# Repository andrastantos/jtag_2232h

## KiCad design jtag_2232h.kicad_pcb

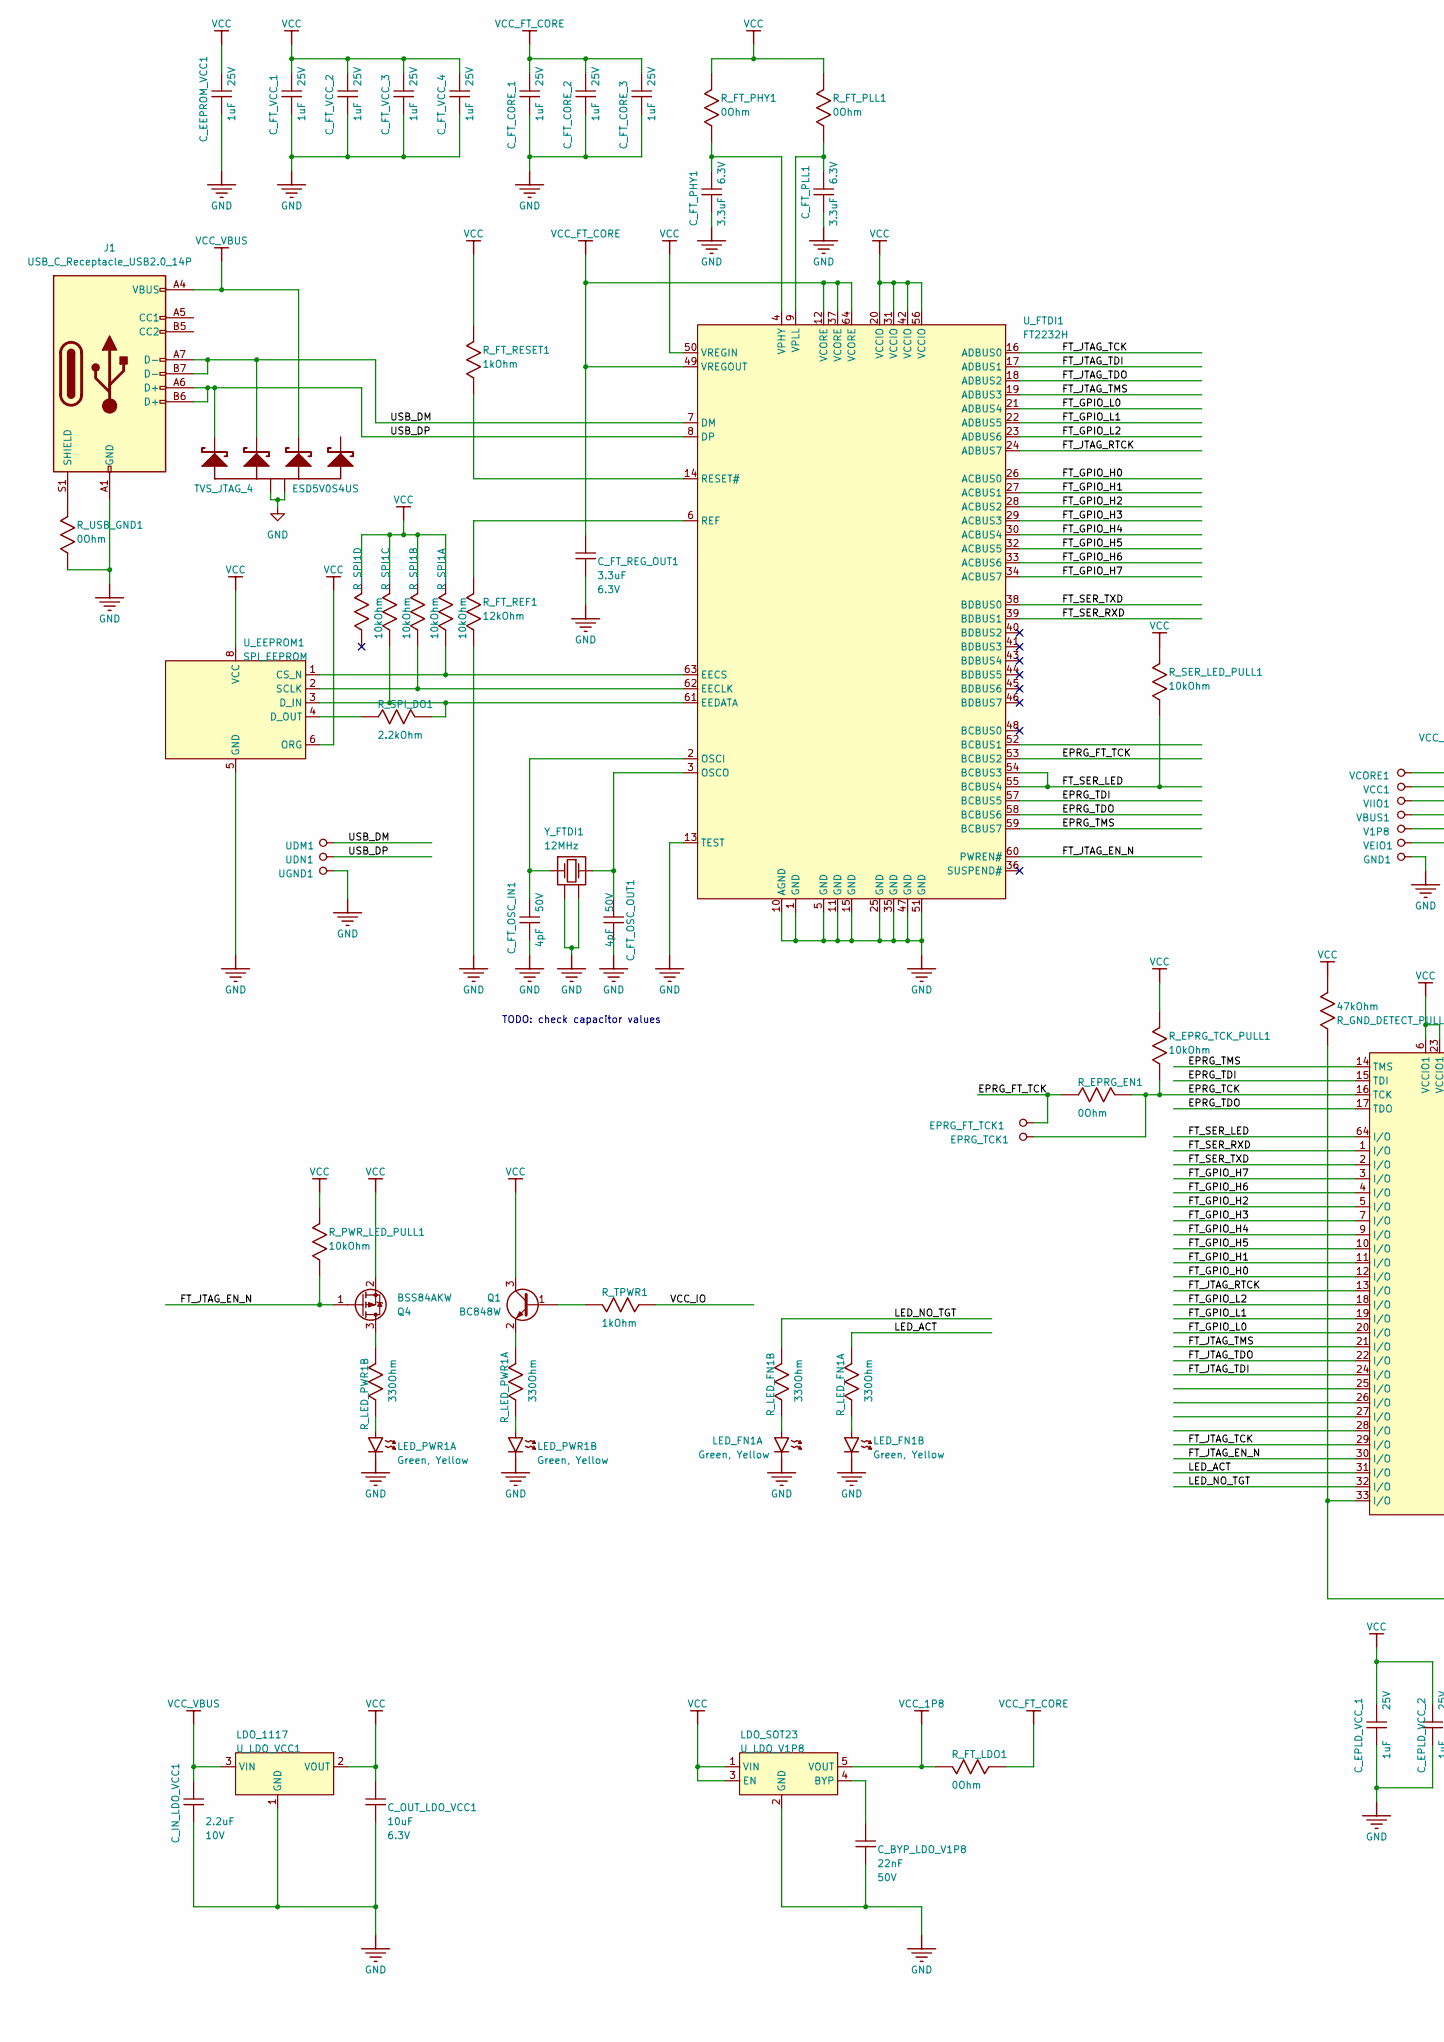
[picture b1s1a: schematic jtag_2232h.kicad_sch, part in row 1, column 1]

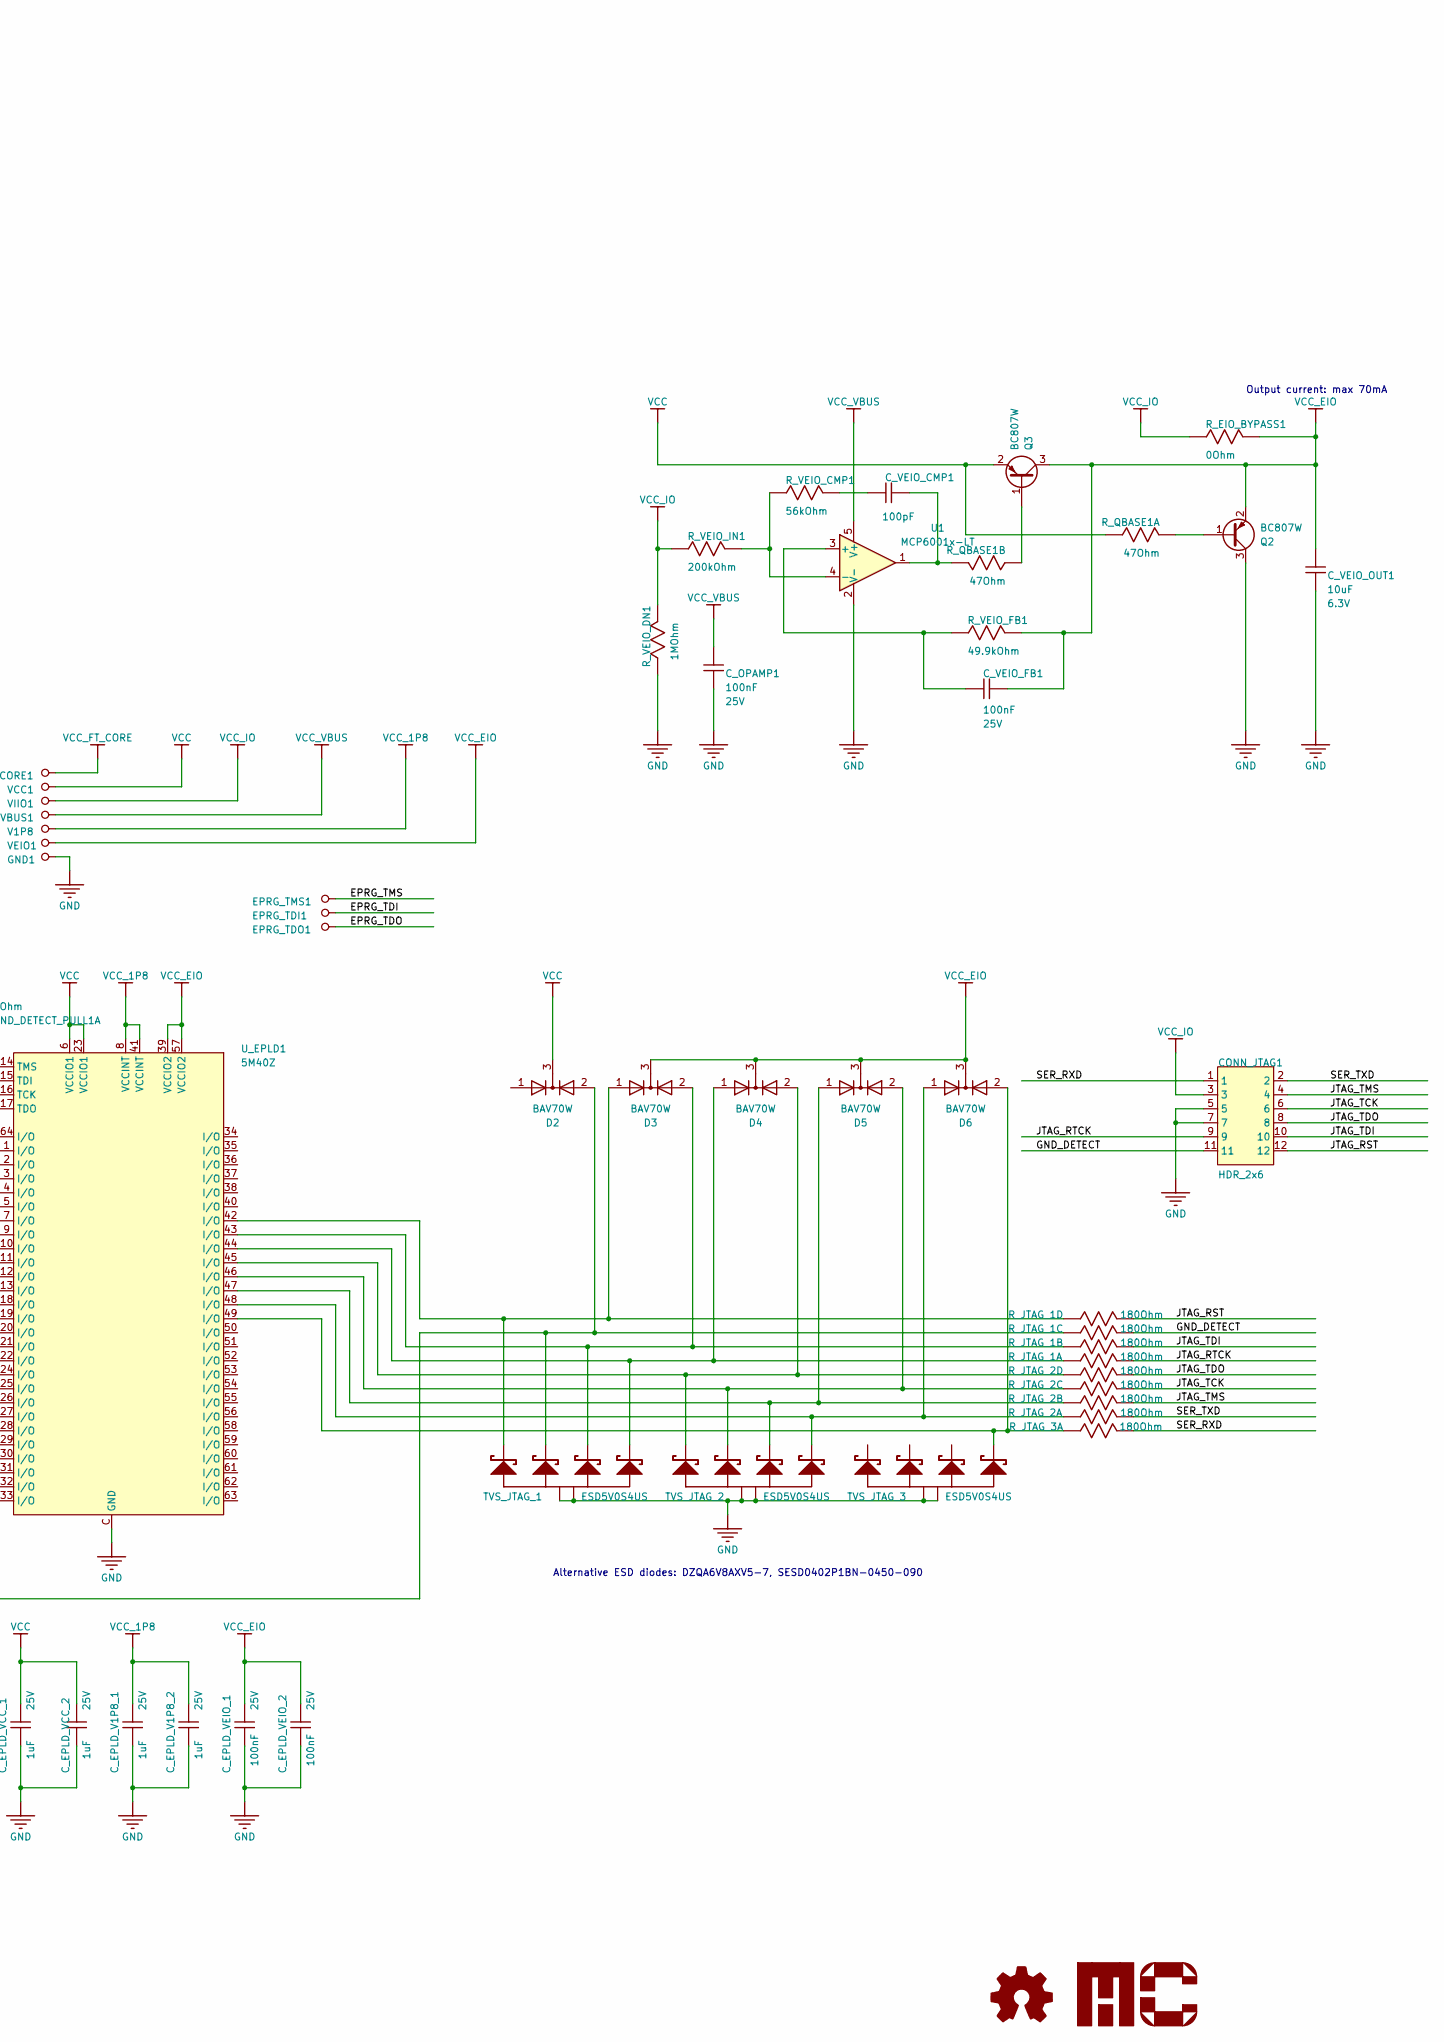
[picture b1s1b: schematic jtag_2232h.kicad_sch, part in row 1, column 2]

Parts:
CONN_JTAG1: HDR_2x6; RCP_1P27_2X6_EDGE; MANUFACTURER PART NUMBER M50-3000645
C_BYP_LDO_V1P8: 22nF; C_0603_1608Metric_Pad1.08x0.95mm_HandSolder; VOLTAGE - RATED 50V; TOLERANCE +/-20%; MANUFACTURER PART NUMBER C1608X7R1H223M; DIGI-KEY PART NUMBER 445-5092-1-ND
C_EEPROM_VCC1: 1uF; C_0603_1608Metric_Pad1.08x0.95mm_HandSolder; VOLTAGE - RATED 25V; TOLERANCE +/-10%; MANUFACTURER PART NUMBER C1608X5R1E105K; DIGI-KEY PART NUMBER 445-5146-1-ND
C_EPLD_V1P8_1, C_EPLD_V1P8_2: 1uF; C_0603_1608Metric_Pad1.08x0.95mm_HandSolder; VOLTAGE - RATED 25V; TOLERANCE +/-10%; MANUFACTURER PART NUMBER C1608X5R1E105K; DIGI-KEY PART NUMBER 445-5146-1-ND
C_EPLD_VCC_1, C_EPLD_VCC_2: 1uF; C_0603_1608Metric_Pad1.08x0.95mm_HandSolder; VOLTAGE - RATED 25V; TOLERANCE +/-10%; MANUFACTURER PART NUMBER C1608X5R1E105K; DIGI-KEY PART NUMBER 445-5146-1-ND
C_EPLD_VEIO_1, C_EPLD_VEIO_2: 100nF; C_0603_1608Metric_Pad1.08x0.95mm_HandSolder; VOLTAGE - RATED 25V; TOLERANCE +/-10%; MANUFACTURER PART NUMBER C1608X7R1E104K; DIGI-KEY PART NUMBER 445-1316-1-ND
C_FT_CORE_1, C_FT_CORE_2, C_FT_CORE_3: 1uF; C_0603_1608Metric_Pad1.08x0.95mm_HandSolder; VOLTAGE - RATED 25V; TOLERANCE +/-10%; MANUFACTURER PART NUMBER C1608X5R1E105K; DIGI-KEY PART NUMBER 445-5146-1-ND
C_FT_OSC_IN1: 4pF; C_0603_1608Metric_Pad1.08x0.95mm_HandSolder; VOLTAGE - RATED 50V; TOLERANCE +/-0.25pF; MANUFACTURER PART NUMBER C1608C0G1H040C; DIGI-KEY PART NUMBER 445-5029-1-ND
C_FT_OSC_OUT1: 4pF; C_0603_1608Metric_Pad1.08x0.95mm_HandSolder; VOLTAGE - RATED 50V; TOLERANCE +/-0.25pF; MANUFACTURER PART NUMBER C1608C0G1H040C; DIGI-KEY PART NUMBER 445-5029-1-ND
C_FT_PHY1: 3.3uF; C_0603_1608Metric_Pad1.08x0.95mm_HandSolder; VOLTAGE - RATED 6.3V; TOLERANCE +/-10%; MANUFACTURER PART NUMBER C1608X5R0J335K; DIGI-KEY PART NUMBER 445-5176-1-ND
C_FT_PLL1: 3.3uF; C_0603_1608Metric_Pad1.08x0.95mm_HandSolder; VOLTAGE - RATED 6.3V; TOLERANCE +/-10%; MANUFACTURER PART NUMBER C1608X5R0J335K; DIGI-KEY PART NUMBER 445-5176-1-ND
C_FT_REG_OUT1: 3.3uF; C_0603_1608Metric_Pad1.08x0.95mm_HandSolder; VOLTAGE - RATED 6.3V; TOLERANCE +/-10%; MANUFACTURER PART NUMBER C1608X5R0J335K; DIGI-KEY PART NUMBER 445-5176-1-ND
C_FT_VCC_1, C_FT_VCC_2, C_FT_VCC_3, C_FT_VCC_4: 1uF; C_0603_1608Metric_Pad1.08x0.95mm_HandSolder; VOLTAGE - RATED 25V; TOLERANCE +/-10%; MANUFACTURER PART NUMBER C1608X5R1E105K; DIGI-KEY PART NUMBER 445-5146-1-ND
C_IN_LDO_VCC1: 2.2uF; C_0603_1608Metric_Pad1.08x0.95mm_HandSolder; VOLTAGE - RATED 10V; TOLERANCE +/-10%; MANUFACTURER PART NUMBER C1608X5R1A225K; DIGI-KEY PART NUMBER 445-5166-1-ND
C_OPAMP1: 100nF; C_0603_1608Metric_Pad1.08x0.95mm_HandSolder; VOLTAGE - RATED 25V; TOLERANCE +/-10%; MANUFACTURER PART NUMBER C1608X7R1E104K; DIGI-KEY PART NUMBER 445-1316-1-ND
C_OUT_LDO_VCC1: 10uF; C_0603_1608Metric_Pad1.08x0.95mm_HandSolder; VOLTAGE - RATED 6.3V; TOLERANCE +/-20%; MANUFACTURER PART NUMBER C1608X5R0J106M; DIGI-KEY PART NUMBER 445-4112-1-ND
C_VEIO_CMP1: 100pF; C_0603_1608Metric_Pad1.08x0.95mm_HandSolder; VOLTAGE - RATED 50V; TOLERANCE +/-5%; MANUFACTURER PART NUMBER C1608C0G1H101J; DIGI-KEY PART NUMBER 445-1281-1-ND
C_VEIO_FB1: 100nF; C_0603_1608Metric_Pad1.08x0.95mm_HandSolder; VOLTAGE - RATED 25V; TOLERANCE +/-10%; MANUFACTURER PART NUMBER C1608X7R1E104K; DIGI-KEY PART NUMBER 445-1316-1-ND
C_VEIO_OUT1: 10uF; C_0603_1608Metric_Pad1.08x0.95mm_HandSolder; VOLTAGE - RATED 6.3V; TOLERANCE +/-20%; MANUFACTURER PART NUMBER C1608X5R0J106M; DIGI-KEY PART NUMBER 445-4112-1-ND
D2, D3, D4, D5, D6: BAV70W; SOT-323_SC-70
EPRG_FT_TCK1: Test_Point; TEST_POINT_100
EPRG_TCK1: Test_Point; TEST_POINT_100
EPRG_TDI1: Test_Point; TEST_POINT_100
EPRG_TDO1: Test_Point; TEST_POINT_100
EPRG_TMS1: Test_Point; TEST_POINT_100
GND1: Test_Point; TEST_POINT_100
J1: USB_C_Receptacle_USB2.0_14P; USB_C_Receptacle_HRO_TYPE-C-31-M-12; mpn USB4215-03-A
LED_FN1: LED_2; LEDX2_150X160X55; MANUFACTURER PART NUMBER APTB1612YSGC-F01
LED_PWR1: LED_2; LEDX2_150X160X55; MANUFACTURER PART NUMBER APTB1612YSGC-F01
LOGO1: MC_logo_micro
Q1: BC848W; SOT-323_SC-70
Q2, Q3: BC807W; SOT-323_SC-70
Q4: BSS84AKW; SOT-323_SC-70
R_EIO_BYPASS1: 0Ohm; R_0603_1608Metric_Pad0.98x0.95mm_HandSolder; TOLERANCE Jumper; MANUFACTURER PART NUMBER RMCF0603ZT0R00; DIGI-KEY PART NUMBER RMCF0603ZT0R00CT-ND
R_EPRG_EN1: 0Ohm; R_0603_1608Metric_Pad0.98x0.95mm_HandSolder; TOLERANCE Jumper; MANUFACTURER PART NUMBER RMCF0603ZT0R00; DIGI-KEY PART NUMBER RMCF0603ZT0R00CT-ND
R_EPRG_TCK_PULL1: 10kOhm; R_0603_1608Metric_Pad0.98x0.95mm_HandSolder; TOLERANCE +/-1%; MANUFACTURER PART NUMBER RMCF0603FT10K0; DIGI-KEY PART NUMBER RMCF0603FT10K0CT-ND
R_FT_LDO1: 0Ohm; R_0603_1608Metric_Pad0.98x0.95mm_HandSolder; TOLERANCE Jumper; MANUFACTURER PART NUMBER RMCF0603ZT0R00; DIGI-KEY PART NUMBER RMCF0603ZT0R00CT-ND
R_FT_PHY1: 0Ohm; R_0603_1608Metric_Pad0.98x0.95mm_HandSolder; TOLERANCE Jumper; MANUFACTURER PART NUMBER RMCF0603ZT0R00; DIGI-KEY PART NUMBER RMCF0603ZT0R00CT-ND
R_FT_PLL1: 0Ohm; R_0603_1608Metric_Pad0.98x0.95mm_HandSolder; TOLERANCE Jumper; MANUFACTURER PART NUMBER RMCF0603ZT0R00; DIGI-KEY PART NUMBER RMCF0603ZT0R00CT-ND
R_FT_REF1: 12kOhm; R_0603_1608Metric_Pad0.98x0.95mm_HandSolder; TOLERANCE +/-1%; MANUFACTURER PART NUMBER RMCF0603FT12K0; DIGI-KEY PART NUMBER RMCF0603FT12K0CT-ND
R_FT_RESET1: 1kOhm; R_0603_1608Metric_Pad0.98x0.95mm_HandSolder; TOLERANCE +/-1%; MANUFACTURER PART NUMBER RMCF0603FT1K00; DIGI-KEY PART NUMBER RMCF0603FT1K00CT-ND
R_GND_DETECT_PULL1: 47kOhm; R_Array_Convex_2x0603; TOLERANCE +/-5%; MANUFACTURER PART NUMBER EXB-V4V473JV; DIGI-KEY PART NUMBER Y2473CT-ND
R_JTAG_1, R_JTAG_2: 180Ohm; R_Array_Convex_4x0603; TOLERANCE +/-5%; MANUFACTURER PART NUMBER EXB-V8V181JV; DIGI-KEY PART NUMBER Y4181CT-ND
R_JTAG_3: 180Ohm; R_Array_Convex_2x0603; TOLERANCE +/-5%; MANUFACTURER PART NUMBER EXB-V4V181JV; DIGI-KEY PART NUMBER Y2181CT-ND
R_LED_FN1: 330Ohm; R_Array_Convex_2x0603; TOLERANCE +/-5%; MANUFACTURER PART NUMBER EXB-V4V331JV; DIGI-KEY PART NUMBER Y2331CT-ND
R_LED_PWR1: 330Ohm; R_Array_Convex_2x0603; TOLERANCE +/-5%; MANUFACTURER PART NUMBER EXB-V4V331JV; DIGI-KEY PART NUMBER Y2331CT-ND
R_PWR_LED_PULL1: 10kOhm; R_0603_1608Metric_Pad0.98x0.95mm_HandSolder; TOLERANCE +/-1%; MANUFACTURER PART NUMBER RMCF0603FT10K0; DIGI-KEY PART NUMBER RMCF0603FT10K0CT-ND
R_QBASE1: 47Ohm; R_Array_Convex_2x0603; TOLERANCE +/-5%; MANUFACTURER PART NUMBER EXB-V4V470JV; DIGI-KEY PART NUMBER Y2470CT-ND
R_SER_LED_PULL1: 10kOhm; R_0603_1608Metric_Pad0.98x0.95mm_HandSolder; TOLERANCE +/-1%; MANUFACTURER PART NUMBER RMCF0603FT10K0; DIGI-KEY PART NUMBER RMCF0603FT10K0CT-ND
R_SPI1: 10kOhm; R_Array_Convex_4x0603; TOLERANCE +/-5%; MANUFACTURER PART NUMBER EXB-V8V103JV; DIGI-KEY PART NUMBER Y4103CT-ND
R_SPI_DO1: 2.2kOhm; R_0603_1608Metric_Pad0.98x0.95mm_HandSolder; TOLERANCE +/-5%; MANUFACTURER PART NUMBER RMCF0603JT2K20; DIGI-KEY PART NUMBER RMCF0603JT2K20CT-ND
R_TPWR1: 1kOhm; R_0603_1608Metric_Pad0.98x0.95mm_HandSolder; TOLERANCE +/-1%; MANUFACTURER PART NUMBER RMCF0603FT1K00; DIGI-KEY PART NUMBER RMCF0603FT1K00CT-ND
R_USB_GND1: 0Ohm; R_0603_1608Metric_Pad0.98x0.95mm_HandSolder; TOLERANCE Jumper; MANUFACTURER PART NUMBER RMCF0603ZT0R00; DIGI-KEY PART NUMBER RMCF0603ZT0R00CT-ND
R_VEIO_CMP1: 56kOhm; R_0603_1608Metric_Pad0.98x0.95mm_HandSolder; TOLERANCE +/-5%; MANUFACTURER PART NUMBER RMCF0603JG56K0; DIGI-KEY PART NUMBER RMCF0603JG56K0CT-ND
R_VEIO_DN1: 1MOhm; R_0603_1608Metric_Pad0.98x0.95mm_HandSolder; TOLERANCE +/-1%; MANUFACTURER PART NUMBER RMCF0603FT1M00; DIGI-KEY PART NUMBER RMCF0603FT1M00CT-ND
R_VEIO_FB1: 49.9kOhm; R_0603_1608Metric_Pad0.98x0.95mm_HandSolder; TOLERANCE +/-1%; MANUFACTURER PART NUMBER RMCF0603FT49K9; DIGI-KEY PART NUMBER RMCF0603FT49K9CT-ND
R_VEIO_IN1: 200kOhm; R_0603_1608Metric_Pad0.98x0.95mm_HandSolder; TOLERANCE +/-5%; MANUFACTURER PART NUMBER RMCF0603JT200K; DIGI-KEY PART NUMBER RMCF0603JT200KCT-ND
TVS_JTAG_1, TVS_JTAG_2, TVS_JTAG_3, TVS_JTAG_4: ESD5V0S4US; SOT-363_SC-70-6
U1: MCP6001x-LT; SOT-353_SC-70-5
UDM1: Test_Point; TEST_POINT_100
UDN1: Test_Point; TEST_POINT_100
UGND1: Test_Point; TEST_POINT_100
U_EEPROM1: SPI_EEPROM; TSSOP-8_4.4x3mm_P0.65mm; MANUFACTURER PART NUMBER AT93C46D-TH-B
U_EPLD1: 5M40Z; TSQFP40P900X900X120_HS_64N
U_FTDI1: FT2232H; LQFP-64_10x10mm_P0.5mm
U_LDO_V1P8: LDO_SOT23; SOT-23-5; OUTPUT VOLTAGE (V) 1.8; INPUT VOLTAGE MIN (V) 1.8; MANUFACTURER PART NUMBER PT7M8206B18TA5EX
U_LDO_VCC1: LDO_1117; SOT-89-3_Handsoldering; OUTPUT VOLTAGE (V) 3.3; INPUT VOLTAGE MIN (V) 2.75; MANUFACTURER PART NUMBER AP1117Y33G-13
V1P8: Test_Point; TEST_POINT_100
VBUS1: Test_Point; TEST_POINT_100
VCC1: Test_Point; TEST_POINT_100
VCORE1: Test_Point; TEST_POINT_100
VEIO1: Test_Point; TEST_POINT_100
VIIO1: Test_Point; TEST_POINT_100
Y_FTDI1: XTAL_4P; XTAL_4P_3P2x2P5; TOLERANCE 15ppm

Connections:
/EPRG_FT_TCK: EPRG_FT_TCK1.1, R_EPRG_EN1.1, U_FTDI1.53 (BCBUS2)
/EPRG_TCK: EPRG_TCK1.1, R_EPRG_EN1.2, R_EPRG_TCK_PULL1.1, U_EPLD1.16 (TCK)
/EPRG_TDI: EPRG_TDI1.1, U_EPLD1.15 (TDI), U_FTDI1.57 (BCBUS5)
/EPRG_TDO: EPRG_TDO1.1, U_EPLD1.17 (TDO), U_FTDI1.58 (BCBUS6)
/EPRG_TMS: EPRG_TMS1.1, U_EPLD1.14 (TMS), U_FTDI1.59 (BCBUS7)
/FT_GPIO_H0: U_EPLD1.12 (I/O), U_FTDI1.26 (ACBUS0)
/FT_GPIO_H1: U_EPLD1.11 (I/O), U_FTDI1.27 (ACBUS1)
/FT_GPIO_H2: U_EPLD1.5 (I/O), U_FTDI1.28 (ACBUS2)
/FT_GPIO_H3: U_EPLD1.7 (I/O), U_FTDI1.29 (ACBUS3)
/FT_GPIO_H4: U_EPLD1.9 (I/O), U_FTDI1.30 (ACBUS4)
/FT_GPIO_H5: U_EPLD1.10 (I/O), U_FTDI1.32 (ACBUS5)
/FT_GPIO_H6: U_EPLD1.4 (I/O), U_FTDI1.33 (ACBUS6)
/FT_GPIO_H7: U_EPLD1.3 (I/O), U_FTDI1.34 (ACBUS7)
/FT_GPIO_L0: U_EPLD1.20 (I/O), U_FTDI1.21 (ADBUS4)
/FT_GPIO_L1: U_EPLD1.19 (I/O), U_FTDI1.22 (ADBUS5)
/FT_GPIO_L2: U_EPLD1.18 (I/O), U_FTDI1.23 (ADBUS6)
/FT_JTAG_EN_N: Q4.1 (G), R_PWR_LED_PULL1.1, U_EPLD1.30 (I/O), U_FTDI1.60 (PWREN#)
/FT_JTAG_RTCK: U_EPLD1.13 (I/O), U_FTDI1.24 (ADBUS7)
/FT_JTAG_TCK: U_EPLD1.29 (I/O), U_FTDI1.16 (ADBUS0)
/FT_JTAG_TDI: U_EPLD1.24 (I/O), U_FTDI1.17 (ADBUS1)
/FT_JTAG_TDO: U_EPLD1.22 (I/O), U_FTDI1.18 (ADBUS2)
/FT_JTAG_TMS: U_EPLD1.21 (I/O), U_FTDI1.19 (ADBUS3)
/FT_SER_LED: R_SER_LED_PULL1.1, U_EPLD1.64 (I/O), U_FTDI1.54 (BCBUS3), U_FTDI1.55 (BCBUS4)
/FT_SER_RXD: U_EPLD1.1 (I/O), U_FTDI1.39 (BDBUS1)
/FT_SER_TXD: U_EPLD1.2 (I/O), U_FTDI1.38 (BDBUS0)
/GND_DETECT: CONN_JTAG1.11, R_JTAG_1.6
/JTAG_RST: CONN_JTAG1.12, R_JTAG_1.5
/JTAG_RTCK: CONN_JTAG1.9, R_JTAG_1.8
/JTAG_TCK: CONN_JTAG1.6, R_JTAG_2.6
/JTAG_TDI: CONN_JTAG1.10, R_JTAG_1.7
/JTAG_TDO: CONN_JTAG1.8, R_JTAG_2.5
/JTAG_TMS: CONN_JTAG1.4, R_JTAG_2.7
/LED_ACT: R_LED_FN1.4, U_EPLD1.31 (I/O)
/LED_NO_TGT: R_LED_FN1.3, U_EPLD1.32 (I/O)
/SER_RXD: CONN_JTAG1.1, R_JTAG_3.1
/SER_TXD: CONN_JTAG1.2, R_JTAG_2.8
/USB_DM: J1.A7 (D-), J1.B7 (D-), TVS_JTAG_4.3 (K), UDM1.1, U_FTDI1.7 (DM)
/USB_DP: J1.A6 (D+), J1.B6 (D+), TVS_JTAG_4.1 (K), UDN1.1, U_FTDI1.8 (DP)
GND: CONN_JTAG1.5, CONN_JTAG1.7, C_BYP_LDO_V1P8.1, C_EEPROM_VCC1.2, C_EPLD_V1P8_1.2, C_EPLD_V1P8_2.2, C_EPLD_VCC_1.2, C_EPLD_VCC_2.2, C_EPLD_VEIO_1.2, C_EPLD_VEIO_2.2, C_FT_CORE_1.2, C_FT_CORE_2.2, C_FT_CORE_3.2, C_FT_OSC_IN1.2, C_FT_OSC_OUT1.2, C_FT_PHY1.2, C_FT_PLL1.2, C_FT_REG_OUT1.2, C_FT_VCC_1.2, C_FT_VCC_2.2, C_FT_VCC_3.2, C_FT_VCC_4.2, C_IN_LDO_VCC1.2, C_OPAMP1.2, C_OUT_LDO_VCC1.2, C_VEIO_OUT1.2, GND1.1, J1.A1 (GND), J1.A12 (GND), J1.B1 (GND), J1.B12 (GND), LED_FN1.C1, LED_FN1.C2, LED_PWR1.C1, LED_PWR1.C2, Q2.3 (C), R_FT_REF1.1, R_USB_GND1.1, R_VEIO_DN1.1, TVS_JTAG_1.2 (A), TVS_JTAG_1.5 (A), TVS_JTAG_2.2 (A), TVS_JTAG_2.5 (A), TVS_JTAG_3.2 (A), TVS_JTAG_3.5 (A), TVS_JTAG_4.2 (A), TVS_JTAG_4.5 (A), U1.2 (V-), UGND1.1, U_EEPROM1.5 (GND), U_EPLD1.C (GND), U_FTDI1.1 (GND), U_FTDI1.5 (GND), U_FTDI1.10 (AGND), U_FTDI1.11 (GND), U_FTDI1.13 (TEST), U_FTDI1.15 (GND), U_FTDI1.25 (GND), U_FTDI1.35 (GND), U_FTDI1.47 (GND), U_FTDI1.51 (GND), U_LDO_V1P8.2 (GND), U_LDO_VCC1.1 (GND), Y_FTDI1.2, Y_FTDI1.4
unnamed: C_VEIO_CMP1.1, R_VEIO_CMP1.2
unnamed: C_VEIO_CMP1.2, R_QBASE1.2, U1.1
unnamed: D2.2 (A), R_GND_DETECT_PULL1.4, R_JTAG_1.3, TVS_JTAG_1.3 (K), U_EPLD1.33 (I/O)
unnamed: D3.1 (A), R_JTAG_1.4, TVS_JTAG_1.1 (K), U_EPLD1.42 (I/O)
unnamed: D3.2 (A), R_JTAG_1.2, TVS_JTAG_1.4 (K), U_EPLD1.43 (I/O)
unnamed: D4.1 (A), R_JTAG_1.1, TVS_JTAG_1.6 (K), U_EPLD1.44 (I/O)
unnamed: D4.2 (A), R_JTAG_2.4, TVS_JTAG_2.1 (K), U_EPLD1.45 (I/O)
unnamed: D5.1 (A), R_JTAG_2.2, TVS_JTAG_2.4 (K), U_EPLD1.47 (I/O)
unnamed: D5.2 (A), R_JTAG_2.3, TVS_JTAG_2.3 (K), U_EPLD1.46 (I/O)
unnamed: D6.1 (A), R_JTAG_2.1, TVS_JTAG_2.6 (K), U_EPLD1.48 (I/O)
unnamed: D6.2 (A), R_JTAG_3.4, TVS_JTAG_3.6 (K), U_EPLD1.49 (I/O)
unnamed: J1.S1 (SHIELD), R_USB_GND1.2
unnamed: LED_FN1.A1, R_LED_FN1.2
unnamed: LED_FN1.A2, R_LED_FN1.1
unnamed: LED_PWR1.A1, R_LED_PWR1.2
unnamed: LED_PWR1.A2, R_LED_PWR1.1
unnamed: Q1.1 (B), R_TPWR1.2
unnamed: Q1.2 (E), R_LED_PWR1.4
unnamed: Q2.1 (B), R_QBASE1.1
unnamed: Q3.1 (B), R_QBASE1.3
unnamed: Q4.3 (D), R_LED_PWR1.3
unnamed: C_VEIO_FB1.1, R_VEIO_FB1.1, U1.3 (+)
unnamed: R_VEIO_CMP1.1, R_VEIO_IN1.2, U1.4 (-)
unnamed: R_SPI1.1, U_EEPROM1.1 (CS_N), U_FTDI1.63 (EECS)
unnamed: R_SPI1.3, R_SPI_DO1.2, U_EEPROM1.3 (D_IN), U_FTDI1.61 (EEDATA)
unnamed: R_SPI_DO1.1, U_EEPROM1.4 (D_OUT)
unnamed: R_SPI1.2, U_EEPROM1.2 (SCLK), U_FTDI1.62 (EECLK)
unnamed: C_FT_OSC_IN1.1, U_FTDI1.2 (OSCI), Y_FTDI1.1
unnamed: C_FT_OSC_OUT1.1, U_FTDI1.3 (OSCO), Y_FTDI1.3
unnamed: R_FT_REF1.2, U_FTDI1.6 (REF)
unnamed: R_FT_RESET1.1, U_FTDI1.14 (RESET#)
unnamed: C_FT_PHY1.1, R_FT_PHY1.1, U_FTDI1.4 (VPHY)
unnamed: C_FT_PLL1.1, R_FT_PLL1.1, U_FTDI1.9 (VPLL)
unnamed: C_BYP_LDO_V1P8.2, U_LDO_V1P8.4 (BYP)
VCC: C_EEPROM_VCC1.1, C_EPLD_VCC_1.1, C_EPLD_VCC_2.1, C_FT_VCC_1.1, C_FT_VCC_2.1, C_FT_VCC_3.1, C_FT_VCC_4.1, C_OUT_LDO_VCC1.1, D2.3 (K), Q1.3 (C), Q3.2 (E), Q4.2 (S), R_EPRG_TCK_PULL1.2, R_FT_PHY1.2, R_FT_PLL1.2, R_FT_RESET1.2, R_GND_DETECT_PULL1.1, R_PWR_LED_PULL1.2, R_QBASE1.4, R_SER_LED_PULL1.2, R_SPI1.5, R_SPI1.6, R_SPI1.7, R_SPI1.8, U_EEPROM1.6 (ORG), U_EEPROM1.8 (VCC), U_EPLD1.6 (VCCIO1), U_EPLD1.23 (VCCIO1), U_FTDI1.20 (VCCIO), U_FTDI1.31 (VCCIO), U_FTDI1.42 (VCCIO), U_FTDI1.50 (VREGIN), U_FTDI1.56 (VCCIO), U_LDO_V1P8.1 (VIN), U_LDO_V1P8.3 (EN), U_LDO_VCC1.2 (VOUT), VCC1.1
VCC_1P8: C_EPLD_V1P8_1.1, C_EPLD_V1P8_2.1, R_FT_LDO1.2, U_EPLD1.8 (VCCINT), U_EPLD1.41 (VCCINT), U_LDO_V1P8.5 (VOUT), V1P8.1
VCC_EIO: C_EPLD_VEIO_1.1, C_EPLD_VEIO_2.1, C_VEIO_FB1.2, C_VEIO_OUT1.1, D3.3 (K), D4.3 (K), D5.3 (K), D6.3 (K), Q2.2 (E), Q3.3 (C), R_EIO_BYPASS1.2, R_VEIO_FB1.2, U_EPLD1.39 (VCCIO2), U_EPLD1.57 (VCCIO2), VEIO1.1
VCC_FT_CORE: C_FT_CORE_1.1, C_FT_CORE_2.1, C_FT_CORE_3.1, C_FT_REG_OUT1.1, R_FT_LDO1.1, U_FTDI1.12 (VCORE), U_FTDI1.37 (VCORE), U_FTDI1.49 (VREGOUT), U_FTDI1.64 (VCORE), VCORE1.1
VCC_IO: CONN_JTAG1.3, R_EIO_BYPASS1.1, R_TPWR1.1, R_VEIO_DN1.2, R_VEIO_IN1.1, VIIO1.1
VCC_VBUS: C_IN_LDO_VCC1.1, C_OPAMP1.1, J1.A4 (VBUS), J1.A9 (VBUS), J1.B4 (VBUS), J1.B9 (VBUS), TVS_JTAG_4.4 (K), U1.5 (V+), U_LDO_VCC1.3 (VIN), VBUS1.1

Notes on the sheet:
Output current: max 70mA
TODO: check capacitor values
Alternative ESD diodes: DZQA6V8AXV5-7, SESD0402P1BN-0450-090

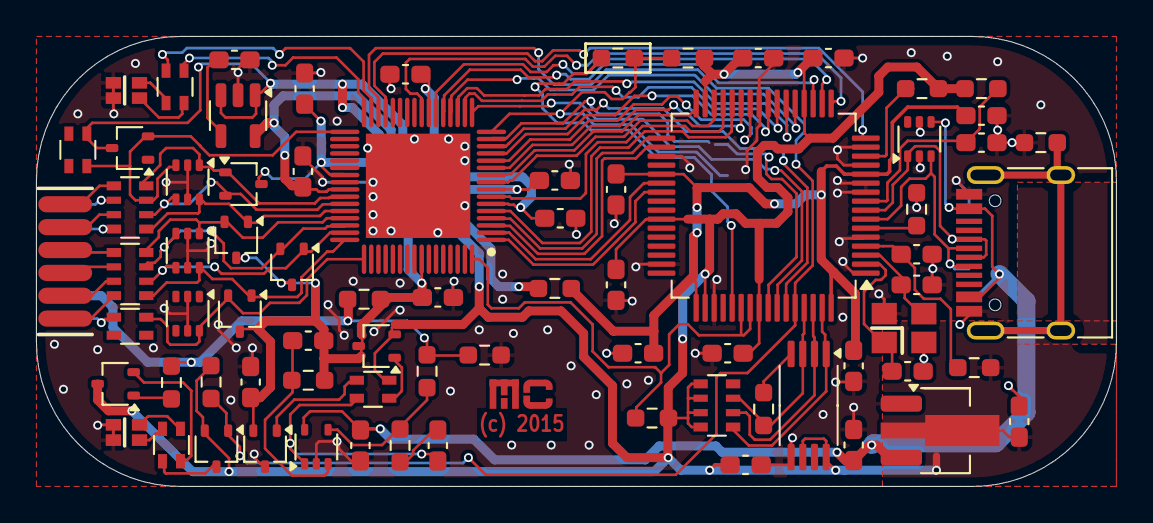
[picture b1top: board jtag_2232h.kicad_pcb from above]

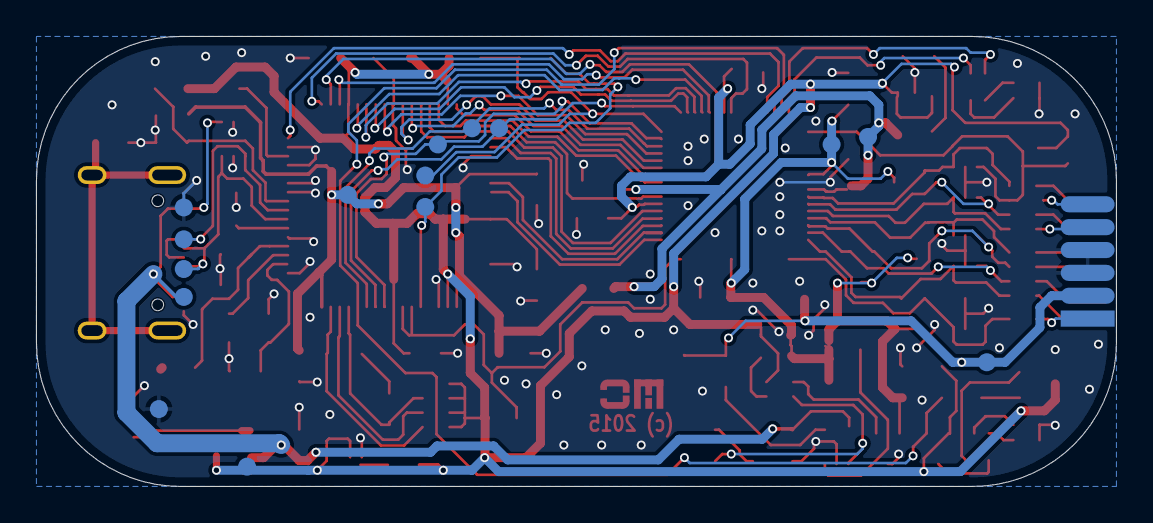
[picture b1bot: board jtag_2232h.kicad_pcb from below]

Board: 2 copper layers, 60.0 x 25.0 mm, 91 parts (15 on the bottom side), 79 nets.

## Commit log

2024-08-21 Another import attempt.
2024-08-22 Annotated with modified KiCAD
2024-08-22 Cleared all DRCs, mostly fixed up library.
2024-09-02 Now using USB-C connector.
    Also using much more KiCAD-like components.

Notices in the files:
jtag_2232h.kicad_pcb:
(c) 2015
